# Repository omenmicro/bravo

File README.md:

# OMEN BRAVO

As-easy-as-possible, but still expandable single board computer with 65C02 CPU.

- [Essential ICs on AliExpress](https://alitronik.com/omen-bravo-pack/)
- [Essential ICs on eBay](https://alitronik.com/omen-bravo-pack-ebay/)

[BOM - Needed parts](./BOM.md)

### Issue 4 is available

Issue 3 adds a 6522 VIA circuit. It features:

- A pair of 8bit parallel ports.
- Each pin of each port can be individually set to the input or to the output.
- Serializer (8 bit shift register)
- A pair of 16bit timer / counter

Issue 4 fixes some problems in the Issue 3 design. See below.

### Issue 3 problem fix

Issue 3 board has some design problems, which is fixed in the Issue 4. Issue 3 is fully working, but you have to manual solder:

- A wire between GND port and a pin 8 of the 74HC138.
- A 180k resistor parallel to the Q1 (between the CPU pins 3 and 37).
- A 47pF capacitor between the CPU pins 1 and 3

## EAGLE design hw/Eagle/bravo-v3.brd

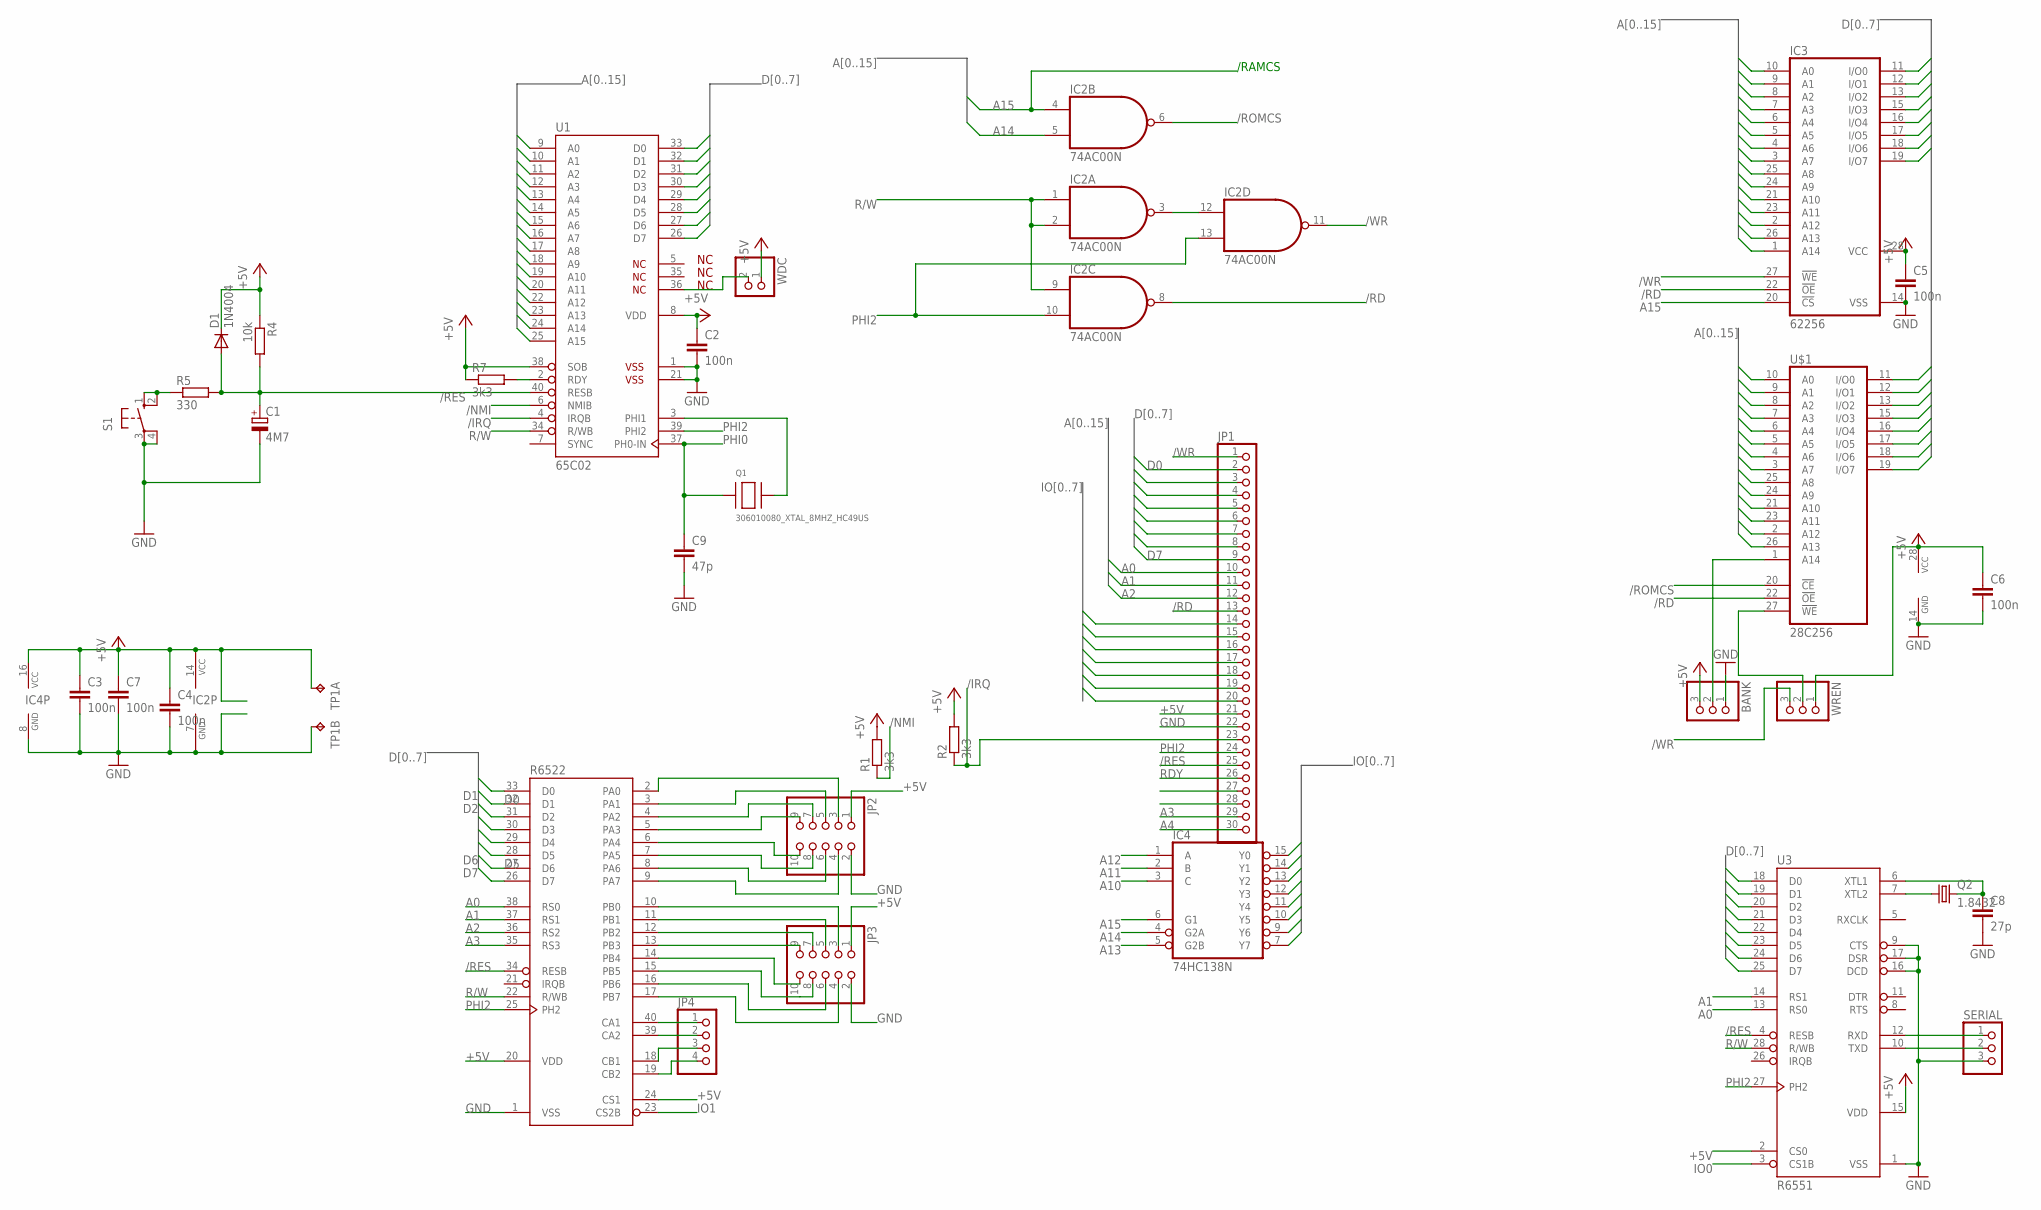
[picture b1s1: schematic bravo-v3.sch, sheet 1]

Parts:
BANK: PINHD-1X3; 1X03
C1: 4M7; E2,5-6
C2, C3, C4, C5, C6, C7: 100n; C025-030X050
C8: 27p; C050-030X075
C9: 47p; C025-030X050
D1: 1N4004; DO41-10
IC2: 74AC00N; DIL14
IC3: 62256; DIL28-6
IC4: 74HC138N; DIL16
JP1: PINHD-1X30; 1X30
JP2, JP3: PINHD-2X5; 2X05
JP4: PINHD-1X4; 1X04
Q1: 306010080_XTAL_8MHZ_HC49US; HC49US
Q2: 1.8432; HC49/S
R1, R2, R7: 3k3; 0207/7
R4: 10k; 0207/7
R5: 330; 0207/7
R6522: G65SC22P; DIP-40
S1: 40-XX; B3F-40XX
SERIAL: PINHD-1X3; 1X03
TP1: TP2P2-38-17; P2-38-17
U1: 65C02; DIP-40
U3: R6551; DIP-28
U$1: 28C256; DIL28
WDC: PINHD-1X2; 1X02
WREN: PINHD-1X3; 1X03

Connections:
+5V: BANK.3, C2.1, C3.1, C4.1, C5.1, C6.1, C7.1, D1.C, IC2.14 (VCC), IC3.28 (VCC), IC4.16 (VCC), JP1.21, JP2.1, JP3.1, R1.2, R2.2, R4.1, R7.1, R6522.20 (VDD), R6522.24 (CS1), TP1.TP-1, U1.8 (VDD), U1.38 (SOB), U3.2 (CS0), U3.15 (VDD), U$1.28 (VCC), WDC.1, WREN.1
/IRQ: JP1.23, R2.1, U1.4 (IRQB)
/NMI: R1.1, U1.6 (NMIB)
/RD: IC2.8 (O), IC3.22 (!OE), JP1.13, U$1.22 (!OE)
/RES: C1.+, D1.A, JP1.25, R4.2, R5.2, R6522.34 (RESB), U1.40 (RESB), U3.4 (RESB)
/ROMCS: IC2.6 (O), U$1.20 (!CE)
/WR: IC2.11 (O), IC3.27 (!WE), JP1.1, WREN.3
A0: IC3.10 (A0), JP1.10, R6522.38 (RS0), U1.9 (A0), U3.13 (RS0), U$1.10 (A0)
A1: IC3.9 (A1), JP1.11, R6522.37 (RS1), U1.10 (A1), U3.14 (RS1), U$1.9 (A1)
A2: IC3.8 (A2), JP1.12, R6522.36 (RS2), U1.11 (A2), U$1.8 (A2)
A3: IC3.7 (A3), JP1.29, R6522.35 (RS3), U1.12 (A3), U$1.7 (A3)
A4: IC3.6 (A4), JP1.30, U1.13 (A4), U$1.6 (A4)
A5: IC3.5 (A5), U1.14 (A5), U$1.5 (A5)
A6: IC3.4 (A6), U1.15 (A6), U$1.4 (A6)
A7: IC3.3 (A7), U1.16 (A7), U$1.3 (A7)
A8: IC3.25 (A8), U1.17 (A8), U$1.25 (A8)
A9: IC3.24 (A9), U1.18 (A9), U$1.24 (A9)
A10: IC3.21 (A10), IC4.3 (C), U1.19 (A10), U$1.21 (A10)
A11: IC3.23 (A11), IC4.2 (B), U1.20 (A11), U$1.23 (A11)
A12: IC3.2 (A12), IC4.1 (A), U1.22 (A12), U$1.2 (A12)
A13: IC3.26 (A13), IC4.5 (G2B), U1.23 (A13), U$1.26 (A13)
A14: IC2.5 (I1), IC3.1 (A14), IC4.4 (G2A), U1.24 (A14)
A15: IC2.4 (I0), IC3.20 (!CS), IC4.6 (G1), U1.25 (A15)
CA1: JP4.1, R6522.40 (CA1)
D0: IC3.11 (I/O0), JP1.2, R6522.33 (D0), U1.33 (D0), U3.18 (D0), U$1.11 (I/O0)
D1: IC3.12 (I/O1), JP1.3, R6522.32 (D1), U1.32 (D1), U3.19 (D1), U$1.12 (I/O1)
D2: IC3.13 (I/O2), JP1.4, R6522.31 (D2), U1.31 (D2), U3.20 (D2), U$1.13 (I/O2)
D3: IC3.15 (I/O3), JP1.5, R6522.30 (D3), U1.30 (D3), U3.21 (D3), U$1.15 (I/O3)
D4: IC3.16 (I/O4), JP1.6, R6522.29 (D4), U1.29 (D4), U3.22 (D4), U$1.16 (I/O4)
D5: IC3.17 (I/O5), JP1.7, R6522.28 (D5), U1.28 (D5), U3.23 (D5), U$1.17 (I/O5)
D6: IC3.18 (I/O6), JP1.8, R6522.27 (D6), U1.27 (D6), U3.24 (D6), U$1.18 (I/O6)
D7: IC3.19 (I/O7), JP1.9, R6522.26 (D7), U1.26 (D7), U3.25 (D7), U$1.19 (I/O7)
GND: BANK.1, C1.-, C2.2, C3.2, C4.2, C5.2, C6.2, C7.2, C8.2, C9.2, IC2.7 (GND), IC3.14 (VSS), IC4.8 (GND), JP1.22, JP2.2, JP3.2, R6522.1 (VSS), S1.3, S1.4 (P1), SERIAL.3, TP1.TP-2, U1.1 (VSS$1), U1.21 (VSS$2), U3.1 (VSS), U3.9 (CTS), U3.16 (DCD), U3.17 (DSR), U$1.14 (GND)
IO0: IC4.15 (Y0), U3.3 (CS1B)
IO1: IC4.14 (Y1), JP1.14, R6522.23 (CS2B)
IO2: IC4.13 (Y2), JP1.15
IO3: IC4.12 (Y3), JP1.16
IO4: IC4.11 (Y4), JP1.17
IO5: IC4.10 (Y5), JP1.18
IO6: IC4.9 (Y6), JP1.19
IO7: IC4.7 (Y7), JP1.20
unnamed: R5.1, S1.1 (S), S1.2 (S1)
unnamed: JP2.9, R6522.5 (PA3)
unnamed: JP2.7, R6522.4 (PA2)
unnamed: JP2.5, R6522.3 (PA1)
unnamed: JP2.3, R6522.2 (PA0)
unnamed: U1.36 (NC$3), WDC.2
unnamed: BANK.2, U$1.1 (A14)
unnamed: IC2.3 (O), IC2.12 (I0)
unnamed: JP2.10, R6522.6 (PA4)
unnamed: JP2.8, R6522.7 (PA5)
unnamed: JP2.6, R6522.8 (PA6)
unnamed: JP2.4, R6522.9 (PA7)
unnamed: JP3.3, R6522.10 (PB0)
unnamed: JP3.5, R6522.11 (PB1)
unnamed: JP3.7, R6522.12 (PB2)
unnamed: JP3.9, R6522.13 (PB3)
unnamed: JP3.10, R6522.14 (PB4)
unnamed: JP3.8, R6522.15 (PB5)
unnamed: JP3.6, R6522.16 (PB6)
unnamed: JP3.4, R6522.17 (PB7)
unnamed: JP4.2, R6522.39 (CA2)
unnamed: JP4.3, R6522.18 (CB1)
unnamed: JP4.4, R6522.19 (CB2)
unnamed: U$1.27 (!WE), WREN.2
unnamed: Q1.P$2, U1.3 (PHI1)
unnamed: SERIAL.1, U3.12 (RXD)
unnamed: SERIAL.2, U3.10 (TXD)
unnamed: Q2.1, U3.7 (XTL2)
unnamed: C8.1, Q2.2, U3.6 (XTL1)
PHI0: C9.1, Q1.P$1, U1.37 (PH0-IN)
PHI2: IC2.10 (I1), IC2.13 (I1), JP1.24, R6522.25 (PH2), U1.39 (PHI2), U3.27 (PH2)
R/W: IC2.1 (I0), IC2.2 (I1), IC2.9 (I0), R6522.22 (R/WB), U1.34 (R/WB), U3.28 (R/WB)
RDY: JP1.26, R7.2, U1.2 (RDY)

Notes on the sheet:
/RAMCS

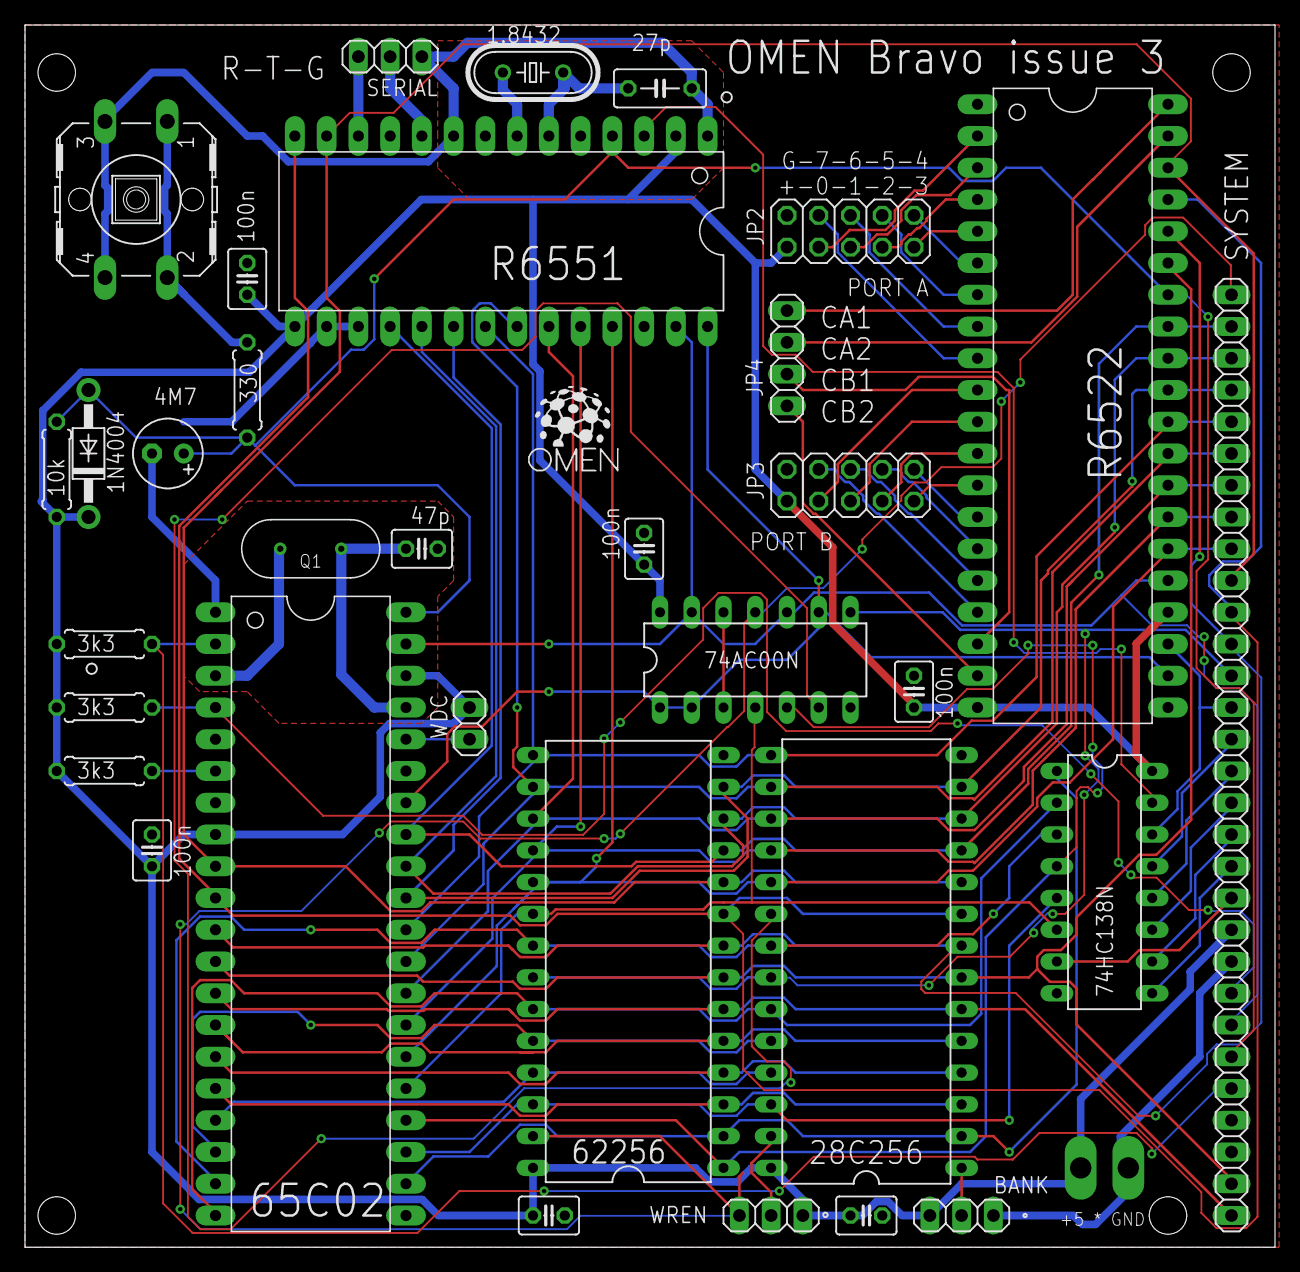
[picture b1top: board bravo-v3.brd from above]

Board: 2 copper layers, 100.0 x 97.8 mm, 34 parts (0 on the bottom side), 74 nets.

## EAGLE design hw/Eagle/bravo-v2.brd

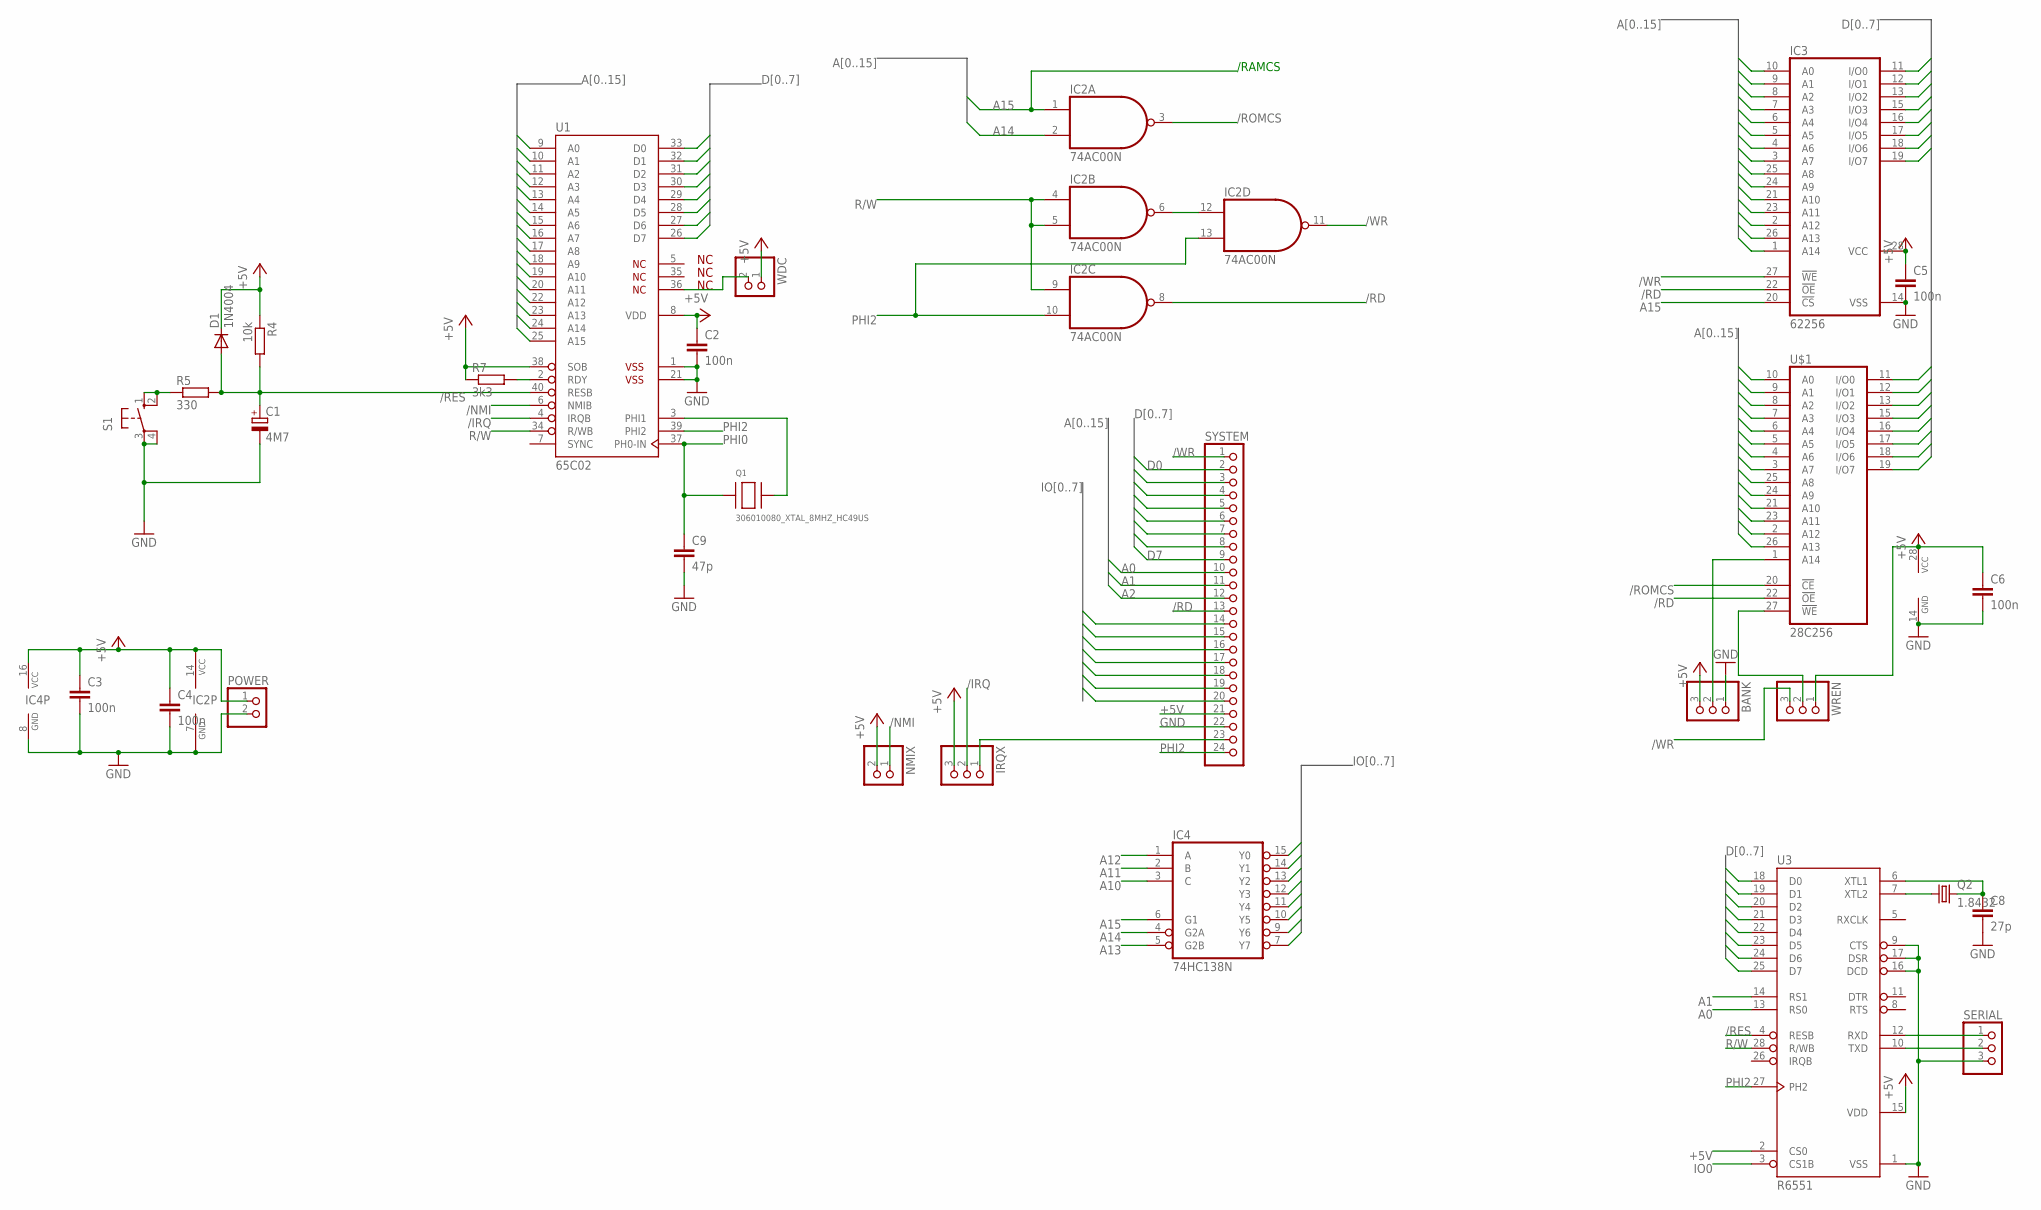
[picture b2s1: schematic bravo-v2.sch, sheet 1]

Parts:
BANK: PINHD-1X3; 1X03
C1: 4M7; E2,5-6
C2, C3, C4, C5, C6: 100n; C025-030X050
C8: 27p; C050-030X075
C9: 47p; C025-030X050
D1: 1N4004; DO41-10
IC2: 74AC00N; DIL14
IC3: 62256; DIL28-6
IC4: 74HC138N; DIL16
IRQX: PINHD-1X3; 1X03
NMIX: PINHD-1X2; 1X02
POWER: PINHD-1X2; 1X02
Q1: 306010080_XTAL_8MHZ_HC49US; HC49US
Q2: 1.8432; HC49/S
R4: 10k; 0207/7
R5: 330; 0207/7
R7: 3k3; 0207/7
S1: 40-XX; B3F-40XX
SERIAL: PINHD-1X3; 1X03
SYSTEM: PINHD-1X24/90; 1X24/90
U1: 65C02; DIP-40
U3: R6551; DIP-28
U$1: 28C256; DIL28
WDC: PINHD-1X2; 1X02
WREN: PINHD-1X3; 1X03

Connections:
+5V: BANK.3, C2.1, C3.1, C4.1, C5.1, C6.1, D1.C, IC2.14 (VCC), IC3.28 (VCC), IC4.16 (VCC), IRQX.3, NMIX.2, POWER.1, R4.1, R7.1, SYSTEM.21, U1.8 (VDD), U1.38 (SOB), U3.2 (CS0), U3.15 (VDD), U$1.28 (VCC), WDC.1, WREN.1
/IRQ: IRQX.2, U1.4 (IRQB)
/NMI: NMIX.1, U1.6 (NMIB)
/RD: IC2.8 (O), IC3.22 (!OE), SYSTEM.13, U$1.22 (!OE)
/RES: C1.+, D1.A, R4.2, R5.2, U1.40 (RESB), U3.4 (RESB)
/ROMCS: IC2.3 (O), U$1.20 (!CE)
/WR: IC2.11 (O), IC3.27 (!WE), SYSTEM.1, WREN.3
A0: IC3.10 (A0), SYSTEM.10, U1.9 (A0), U3.13 (RS0), U$1.10 (A0)
A1: IC3.9 (A1), SYSTEM.11, U1.10 (A1), U3.14 (RS1), U$1.9 (A1)
A2: IC3.8 (A2), SYSTEM.12, U1.11 (A2), U$1.8 (A2)
A3: IC3.7 (A3), U1.12 (A3), U$1.7 (A3)
A4: IC3.6 (A4), U1.13 (A4), U$1.6 (A4)
A5: IC3.5 (A5), U1.14 (A5), U$1.5 (A5)
A6: IC3.4 (A6), U1.15 (A6), U$1.4 (A6)
A7: IC3.3 (A7), U1.16 (A7), U$1.3 (A7)
A8: IC3.25 (A8), U1.17 (A8), U$1.25 (A8)
A9: IC3.24 (A9), U1.18 (A9), U$1.24 (A9)
A10: IC3.21 (A10), IC4.3 (C), U1.19 (A10), U$1.21 (A10)
A11: IC3.23 (A11), IC4.2 (B), U1.20 (A11), U$1.23 (A11)
A12: IC3.2 (A12), IC4.1 (A), U1.22 (A12), U$1.2 (A12)
A13: IC3.26 (A13), IC4.5 (G2B), U1.23 (A13), U$1.26 (A13)
A14: IC2.2 (I1), IC3.1 (A14), IC4.4 (G2A), U1.24 (A14)
A15: IC2.1 (I0), IC3.20 (!CS), IC4.6 (G1), U1.25 (A15)
D0: IC3.11 (I/O0), SYSTEM.2, U1.33 (D0), U3.18 (D0), U$1.11 (I/O0)
D1: IC3.12 (I/O1), SYSTEM.3, U1.32 (D1), U3.19 (D1), U$1.12 (I/O1)
D2: IC3.13 (I/O2), SYSTEM.4, U1.31 (D2), U3.20 (D2), U$1.13 (I/O2)
D3: IC3.15 (I/O3), SYSTEM.5, U1.30 (D3), U3.21 (D3), U$1.15 (I/O3)
D4: IC3.16 (I/O4), SYSTEM.6, U1.29 (D4), U3.22 (D4), U$1.16 (I/O4)
D5: IC3.17 (I/O5), SYSTEM.7, U1.28 (D5), U3.23 (D5), U$1.17 (I/O5)
D6: IC3.18 (I/O6), SYSTEM.8, U1.27 (D6), U3.24 (D6), U$1.18 (I/O6)
D7: IC3.19 (I/O7), SYSTEM.9, U1.26 (D7), U3.25 (D7), U$1.19 (I/O7)
GND: BANK.1, C1.-, C2.2, C3.2, C4.2, C5.2, C6.2, C8.2, C9.2, IC2.7 (GND), IC3.14 (VSS), IC4.8 (GND), POWER.2, S1.3, S1.4 (P1), SERIAL.3, SYSTEM.22, U1.1 (VSS$1), U1.21 (VSS$2), U3.1 (VSS), U3.9 (CTS), U3.16 (DCD), U3.17 (DSR), U$1.14 (GND)
IO0: IC4.15 (Y0), U3.3 (CS1B)
IO1: IC4.14 (Y1), SYSTEM.14
IO2: IC4.13 (Y2), SYSTEM.15
IO3: IC4.12 (Y3), SYSTEM.16
IO4: IC4.11 (Y4), SYSTEM.17
IO5: IC4.10 (Y5), SYSTEM.18
IO6: IC4.9 (Y6), SYSTEM.19
IO7: IC4.7 (Y7), SYSTEM.20
unnamed: R5.1, S1.1 (S), S1.2 (S1)
unnamed: U1.36 (NC$3), WDC.2
unnamed: BANK.2, U$1.1 (A14)
unnamed: IC2.6 (O), IC2.12 (I0)
unnamed: R7.2, U1.2 (RDY)
unnamed: U$1.27 (!WE), WREN.2
unnamed: IRQX.1, SYSTEM.23
unnamed: Q1.P$2, U1.3 (PHI1)
unnamed: SERIAL.1, U3.12 (RXD)
unnamed: SERIAL.2, U3.10 (TXD)
unnamed: Q2.1, U3.7 (XTL2)
unnamed: C8.1, Q2.2, U3.6 (XTL1)
PHI0: C9.1, Q1.P$1, U1.37 (PH0-IN)
PHI2: IC2.10 (I1), IC2.13 (I1), SYSTEM.24, U1.39 (PHI2), U3.27 (PH2)
R/W: IC2.4 (I0), IC2.5 (I1), IC2.9 (I0), U1.34 (R/WB), U3.28 (R/WB)

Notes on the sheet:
/RAMCS

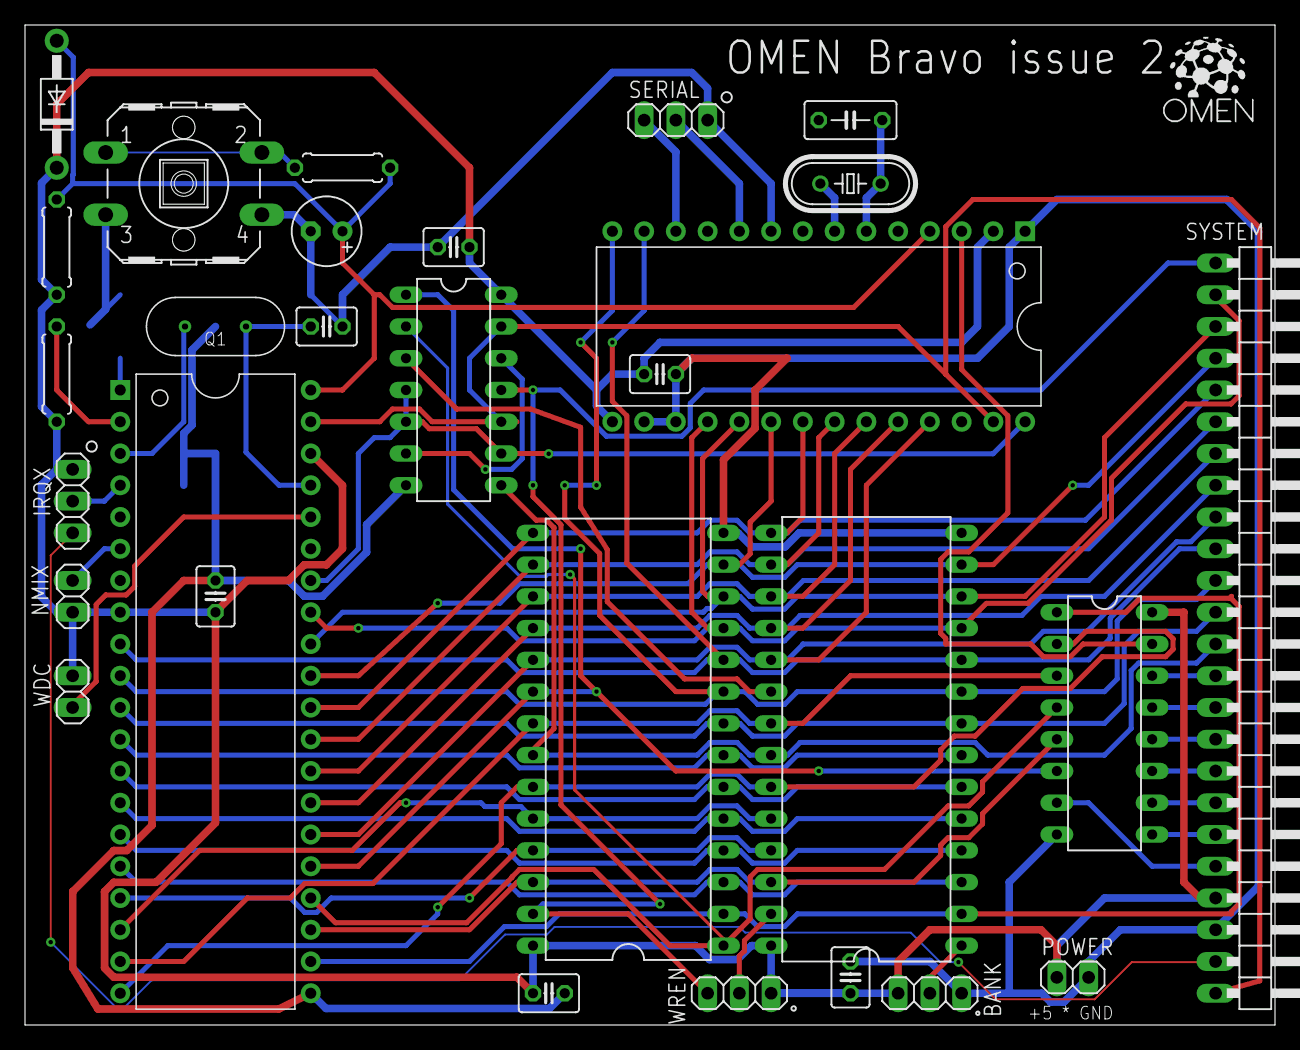
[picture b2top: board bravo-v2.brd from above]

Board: 2 copper layers, 100.0 x 80.0 mm, 29 parts (0 on the bottom side), 55 nets.

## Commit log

2018-08-09 Datasheets
2018-08-28 Badge
2018-09-16 Monitor cmon
2018-09-18 ACIA init
2018-09-21 Manual
2018-10-27 Issue 4
2018-10-27 Issue 4 readme
2018-10-27 Issue 4 gerber files
2018-10-27 README about the news
2019-03-31 packs
2019-03-31 Docs
2019-05-19 contributions
2019-10-12 Patreon
2019-10-13 CMON bin
2022-06-17 SBC2OS
